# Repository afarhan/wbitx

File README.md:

# wifitalkie

A walkie-talkie on WiFi, on an ESP32-C3, that speaks through my.sbitx.net's
VoIP repeater. To my.sbitx.net it is one more radio of its owner's account,
always in the mode VOIP: the dial, FREQ, is the room, and whoever speaks on
that kilohertz, from a zBitx, an sBitx or another talkie, is heard here.

This first one is set from the laptop over USB, a verb a line.

## Build, upload, talk to it

    make                          # arduino-cli, esp32:esp32 3.3.0, ESP32-C3, USB CDC on boot
    make upload PORT=/dev/ttyACM0
    make monitor                  # tools/talkie.py: type verbs
    make check                    # host tests, against zbitxre's accounts/voip.py

`tools/talkie.py STATUS` sends one verb and prints what comes back.

## First time

    WIFI "my ssid" mypassword
    CALL VU2ESE
    FREQ 7074000
    KEY                           # add this at my.sbitx.net as one of your radios
    STATUS                        # SERVICE ONLINE vu2ese-talkie, VOIP 7074 KHZ, 2 HERE

The first connection stretches the key, some seconds; it is kept after that.

## Verbs

    WIFI <ssid> <password>    CALL <callsign>     GRID <locator>
    FREQ <hz>                 SERVER <host> [port]
    KEY                       NEW_KEY (twice within 5 s)
    VOIP ONLINE|OFFLINE       PTT ON|OFF          TONE ON|OFF
    VOL <0-100>               MIC <0-100>         LEVELS ON|OFF
    STATUS                    RESTART

What the talkie says by itself: `WIFI UP`, `SERVICE ...`, `ROOM 7074 KHZ, 3 HERE`,
`HEARD VU3XYZ`, `OVER VU3XYZ`, `BUSY VU3XYZ`, `PTT ON`, `PTT OFF: ONE MINUTE`.

## Wiring (ESP32-C3 SuperMini; pins.h)

| GPIO | |
|---|---|
| 3 (ADC1) | microphone: MAX9814 module output |
| 4 | earbuds: 10 Ω, then an LC low-pass of about 5 kHz (1 mH in series and 1 µF to ground for 32 Ω earbuds; 470 µH and 2.2 µF for 16 Ω), then 220 µF (+ toward the C3) to tip and ring; sleeve to ground |
| 9 | PTT: the BOOT button, to ground |
| 8 | lamp: the board's LED, lit while speaking or hearing |

## Where the protocol is written

zbitxre's `PROTOCOL.md` ("Authentication", "VoIP: the repeater"),
`accounts/voip.py` and `clients/remote/zbitx_remote.c`.
`wifitalkie/sha256.c` is zbitxre's `clients/remote/sha256.c`, as it is.

## Updating over WiFi

`firmware/wifitalkie.ino.bin` is the firmware as `make release` puts it
there, with `firmware/version.txt`, the time it was built.

From GitHub: on the talkie, joined to a network, Settings > Update... >
From github.com, ENTER. It takes the file if it is newer than its own and
restarts into it; otherwise it says Up to date. The serial command
`UPDATE GITHUB` does the same.

Locally, from a phone or laptop: Settings > Update... > Locally on the
talkie, join its access point TALKIE-<callsign>, open 192.168.4.1, type
the four-figure code the talkie shows, choose the file and SEND. The
talkie and the page both show how far it has got; when it says done,
close the page.

Either way, a firmware that does not start goes back to the old one by
itself.

## License

GPL-3.0-or-later; see LICENSE.

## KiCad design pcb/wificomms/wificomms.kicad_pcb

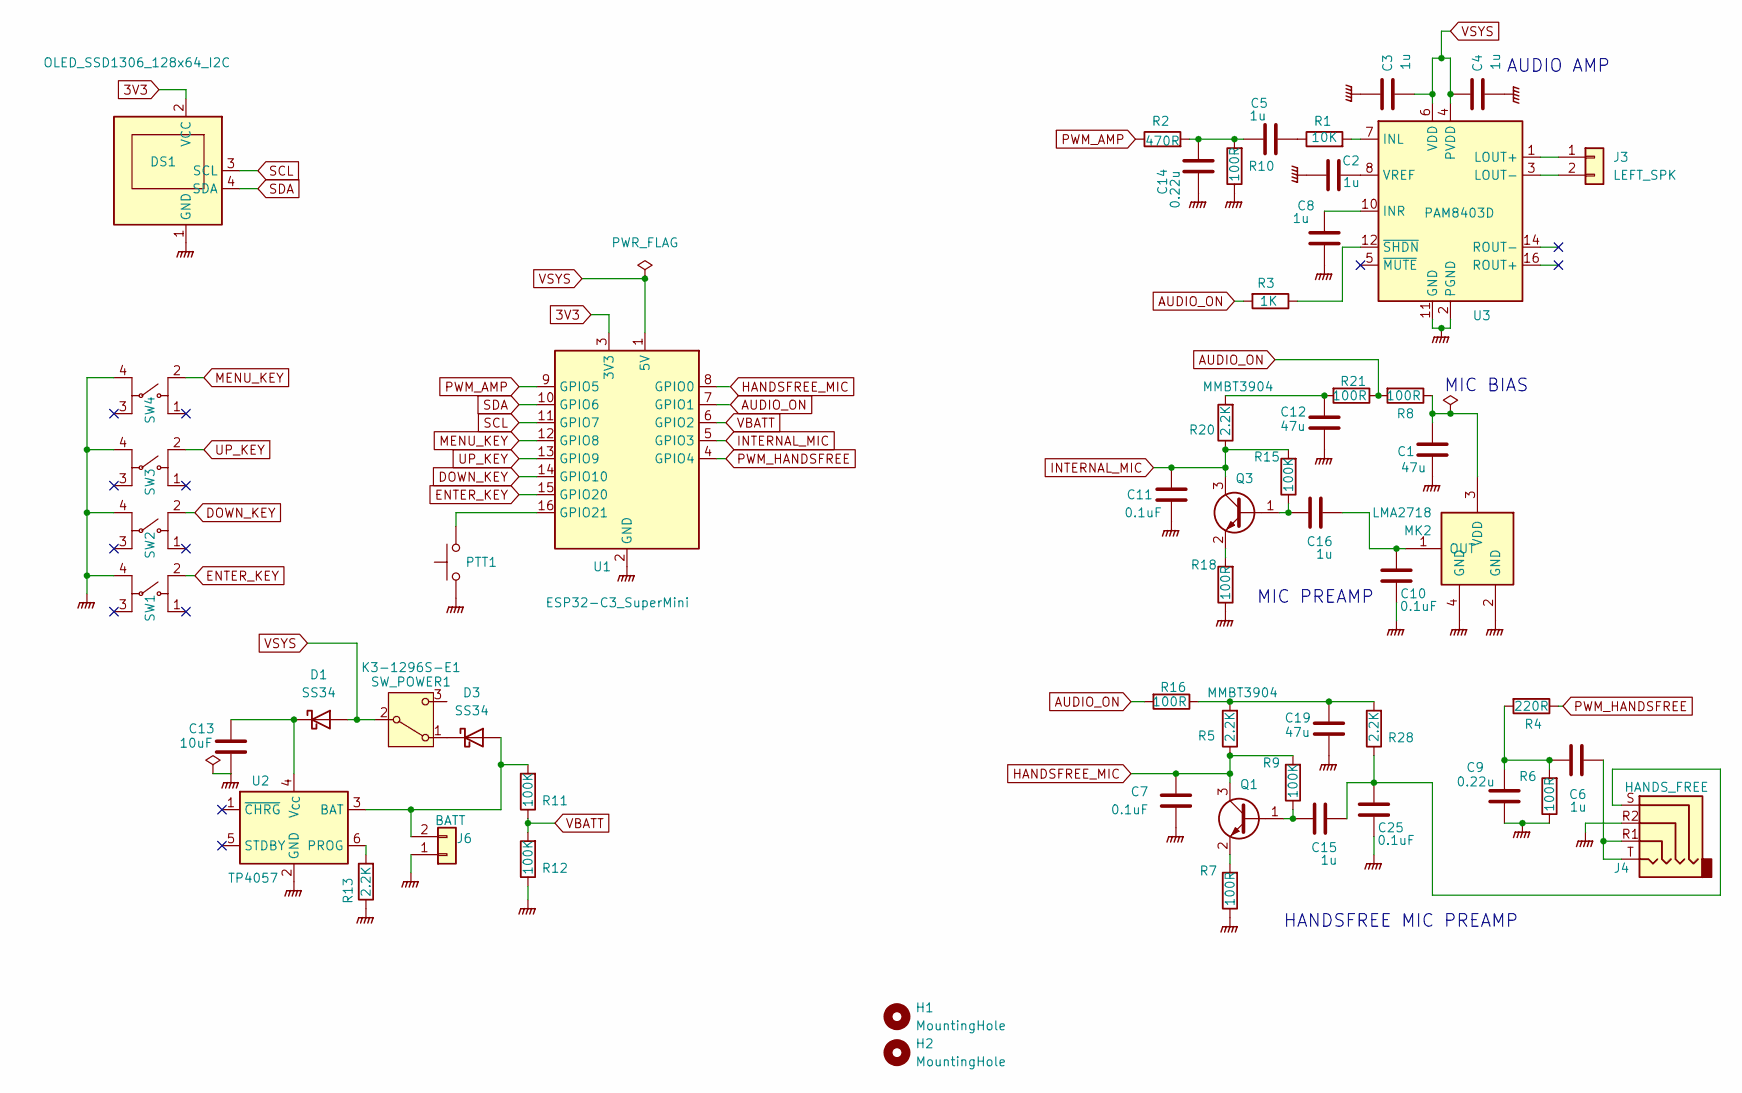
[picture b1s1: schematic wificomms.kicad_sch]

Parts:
C1, C12, C19: 47u; C_0805_2012Metric; LCSC C16780
C2, C3, C4, C5, C8: 1u; C_0805_2012Metric
C6, C15, C16: 1u; C_0805_2012Metric; LCSC C28323
C7, C10, C11, C25: 0.1uF; C_0805_2012Metric; LCSC C49678
C9: 0.22u; C_0805_2012Metric; LCSC C5378
C13: 10uF; C_0805_2012Metric; LCSC C15850
C14: 0.22u; C_0805_2012Metric
D1, D3: SS34; D_SMA; LCSC C8678
DS1: OLED_SSD1306_128x64_I2C
H1, H2: MountingHole; MountingHole_3.2mm_M3
J3: LEFT_SPK; PinHeader_1x02_P2.54mm_Vertical
J4: HANDS_FREE; Jack_3.5mm_PJ320D_Horizontal; LCSC C431535
J6: BATT; JST_PH_S2B-PH-SM4-TB_1x02-1MP_P2.00mm_Horizontal; LCSC C54582899
MK2: LMA2718; MEMS_LMA2718; LCSC C5373222
PTT1: SKRTLAE010; LCSC C110293
Q1, Q3: MMBT3904; SOT-23-3; LCSC C20526
R1: 10K; R_0805_2012Metric
R2: 470R; R_1206_3216Metric
R3: 1K; R_0805_2012Metric; LCSC C17520
R4: 220R; R_0805_2012Metric; LCSC C17557
R5, R13, R20, R28: 2.2K; R_0805_2012Metric; LCSC C17520
R6, R7, R8, R18: 100R; R_0805_2012Metric; LCSC C17408
R9, R15: 100K; R_0805_2012Metric; LCSC C149504
R10: 100R; R_0805_2012Metric
R11, R12: 100K; R_0805_2012Metric; LCSC C17520
R16, R21: 100R; R_0805_2012Metric; LCSC C17415
SW1, SW2, SW3, SW4: B3FS-1010P; LCSC C231324
SW_POWER1: K3-1296S-E1; LCSC C128955
U1: ESP32-C3_SuperMini
U2: TP4057; TSOT-23-6; LCSC C725791
U3: PAM8403D; SO-16_3.9x9.9mm_P1.27mm

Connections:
3V3: DS1.2 (VCC), U1.3 (3V3)
AUDIO_ON: R3.2, R8.2, R16.2, R21.1, U1.7 (GPIO1)
DOWN_KEY: SW2.2, U1.14 (GPIO10)
ENTER_KEY: SW1.2, U1.15 (GPIO20)
GNDPWR: C1.2, C2.1, C3.1, C4.2, C7.1, C8.1, C9.1, C10.1, C11.1, C12.2, C13.2, C14.1, C19.2, C25.1, DS1.1 (GND), J4.R2, J6.1, MK2.2 (GND), MK2.4 (GND), PTT1.1, R6.1, R7.1, R10.1, R12.1, R13.1, R18.1, SW1.4, SW2.4, SW3.4, SW4.4, U1.2 (GND), U2.2 (GND), U3.2 (PGND), U3.11 (GND), U3.15 (PGND)
HANDSFREE_MIC: C7.2, Q1.3 (C), R5.1, R9.2, U1.8 (GPIO0)
INTERNAL_MIC: C11.2, Q3.3 (C), R15.2, R20.1, U1.5 (GPIO3)
MENU_KEY: SW4.2, U1.12 (GPIO8)
unnamed: C5.2, R1.1
unnamed: C6.1, C9.2, R4.2, R6.2
unnamed: C6.2, J4.R1, J4.T
unnamed: C12.1, R20.2, R21.2
unnamed: C5.1, C14.2, R2.2, R10.2
unnamed: C15.2, C25.2, J4.S, R28.1
unnamed: C19.1, R5.2, R16.1, R28.2
unnamed: C13.1, D1.1 (K), U2.4 (V_{CC})
unnamed: D3.2 (A), J6.2, R11.2, U2.3 (BAT)
unnamed: D3.1 (K), SW_POWER1.1 (A)
unnamed: J3.1, U3.1 (LOUT+)
unnamed: J3.2, U3.3 (LOUT-)
unnamed: C10.2, C16.2, MK2.1 (OUT)
unnamed: C1.1, MK2.3 (VDD), R8.1
unnamed: C15.1, Q1.1 (B), R9.1
unnamed: Q1.2 (E), R7.2
unnamed: C16.1, Q3.1 (B), R15.1
unnamed: Q3.2 (E), R18.2
unnamed: PTT1.2, U1.16 (GPIO21)
unnamed: R13.2, U2.6 (PROG)
unnamed: R1.2, U3.7 (INL)
unnamed: C8.2, U3.10 (INR)
unnamed: C2.2, U3.8 (VREF)
unnamed: R3.1, U3.12 (~SHDN)
PWM_AMP: R2.1, U1.9 (GPIO5)
PWM_HANDSFREE: R4.1, U1.4 (GPIO4)
SCL: DS1.3 (SCL), U1.11 (GPIO7)
SDA: DS1.4 (SDA), U1.10 (GPIO6)
UP_KEY: SW3.2, U1.13 (GPIO9)
VBATT: R11.1, R12.2, U1.6 (GPIO2)
VSYS: C3.2, C4.1, D1.2 (A), SW_POWER1.2 (B), U1.1 (5V), U3.4 (PVDD), U3.6 (VDD), U3.13 (PVDD)

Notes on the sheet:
AUDIO AMP
HANDSFREE MIC PREAMP
MIC PREAMP
MIC BIAS

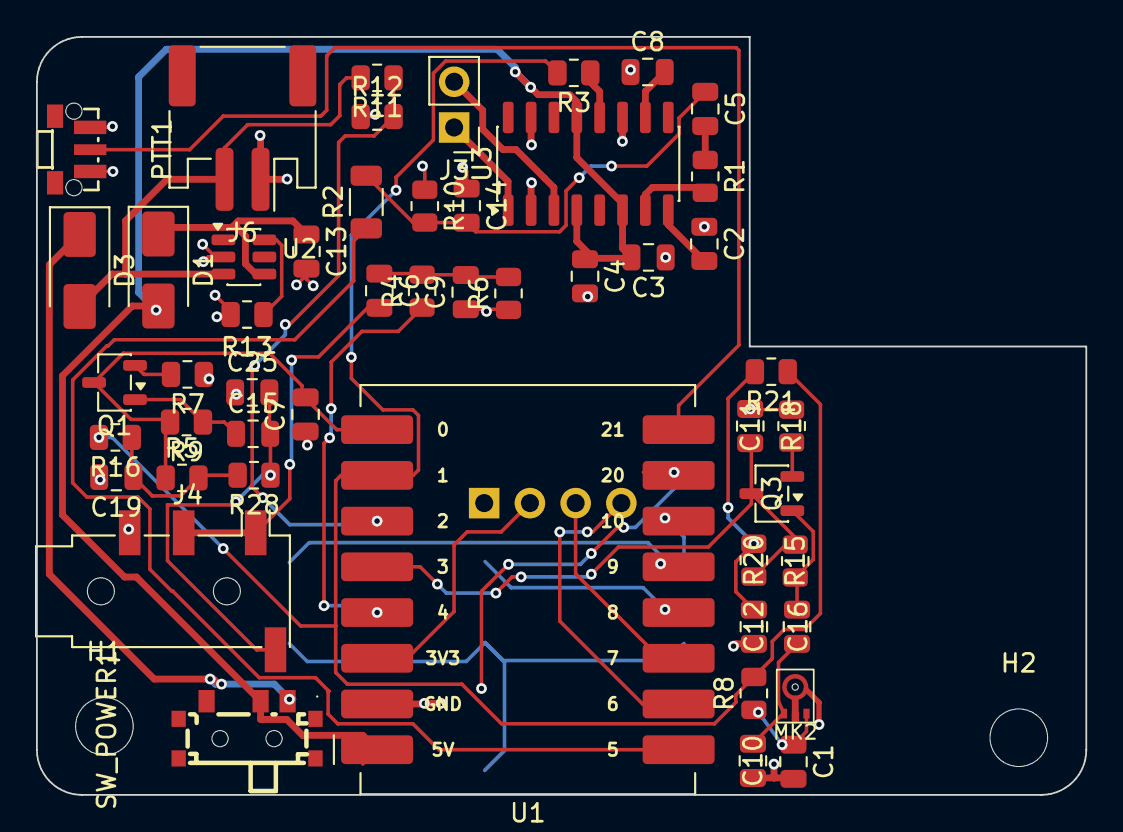
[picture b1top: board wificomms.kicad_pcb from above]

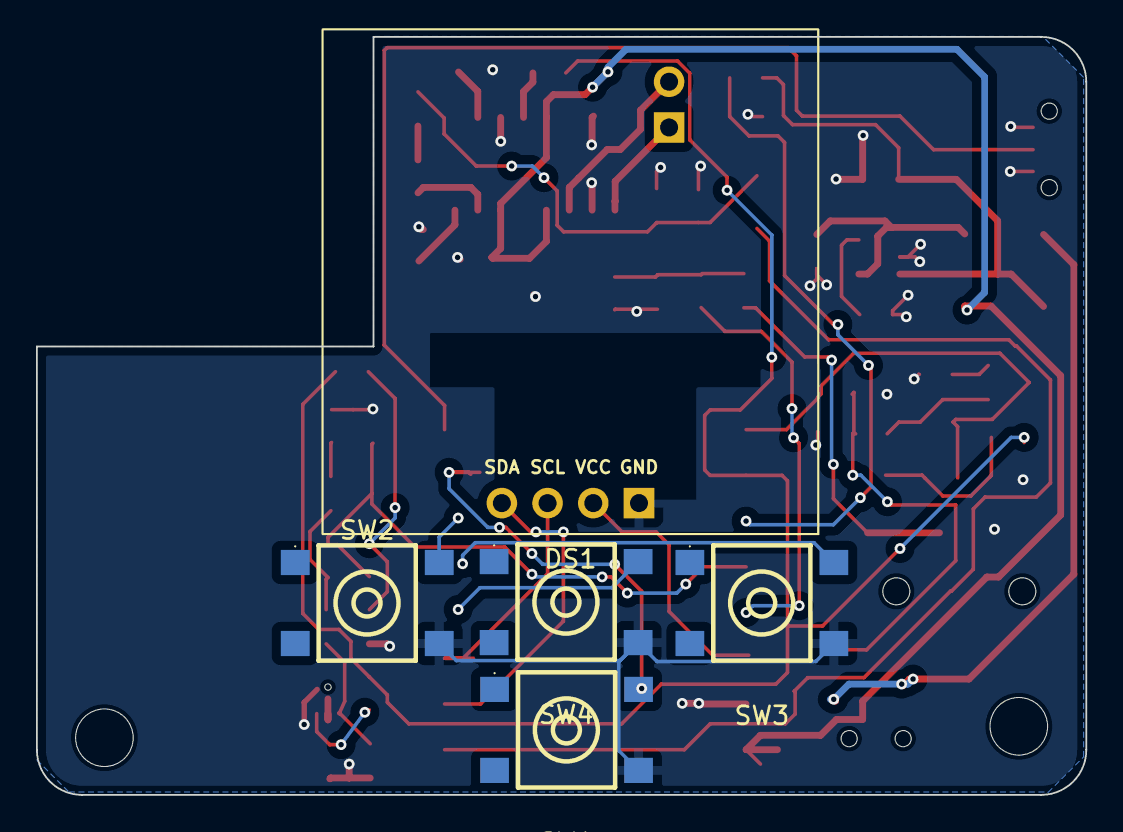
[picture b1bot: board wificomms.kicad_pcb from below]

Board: 2 copper layers, 58.3 x 42.1 mm, 57 parts (5 on the bottom side), 39 nets.

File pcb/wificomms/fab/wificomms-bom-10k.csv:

Comment,Designator,Footprint,LCSC Part #
47u,"C1,C12,C19",C_0805_2012Metric,C16780
1u,"C2,C3,C4,C5,C6,C8,C15,C16",C_0805_2012Metric,C28323
0.1uF,"C7,C10,C11,C25",C_0805_2012Metric,C49678
0.22u,"C9,C14",C_0805_2012Metric,C5378
10uF,C13,C_0805_2012Metric,C15850
SS34,"D1,D3",D_SMA,C8678
HANDS_FREE,J4,Jack_3.5mm_PJ320D_Horizontal,C431535
BATT,J6,JST_PH_S2B-PH-SM4-TB_1x02-1MP_P2.00mm_Horizontal,C54582899
LMA2718,MK2,MEMS_LMA2718,C5373222
SKRTLAE010,PTT1,SKRTLAE010,C110293
MMBT3904,"Q1,Q3",SOT-23-3,C20526
10K,"R1,R11,R12",R_0805_2012Metric,C17414
470R,R2,R_1206_3216Metric,C4502
1K,R3,R_0805_2012Metric,C17513
220R,R4,R_0805_2012Metric,C17557
2.2K,"R5,R13,R20,R28",R_0805_2012Metric,C17520
100R,"R6,R7,R8,R10,R16,R18,R21",R_0805_2012Metric,C17408
100K,"R9,R15",R_0805_2012Metric,C149504
B3FS-1010P,"SW1,SW2,SW3,SW4",B3FS-1010P,C231324
K3-1296S-E1,SW_POWER1,K3-1296S-E1,C128955
TP4057,U2,TSOT-23-6,C725791
PAM8403D,U3,SO-16_3.9x9.9mm_P1.27mm,C5122557

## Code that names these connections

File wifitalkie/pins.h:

// SPDX-License-Identifier: GPL-3.0-or-later
// Copyright (C) 2026 Ashhar Farhan
//
// pins.h — where the talkie's parts go on an ESP32-C3 SuperMini.
//
// The author's map of 31 October 2026, for his PCB. The microphones have to
// be on ADC1, GPIO0 to GPIO4: ADC2 cannot be read while the WiFi is on. The
// front panel, the display and four keys, is GPIO6 to GPIO10 and GPIO20, in
// a row on one edge, for one connector; the keys, top to bottom, MENU, UP,
// DOWN, ENTER. GPIO9 is also the board's BOOT button, so BOOT is UP once
// the board has started; GPIO8 is also its blue lamp, which lights while
// MENU is held, and the talkie's lamp is now on the display. ENTER is the
// PTT on the home page; the PTT key speaks on every page. GPIO4 and GPIO5
// are the headset's left and right.
// GPIO0 is the headset's microphone. GPIO1 powers both microphones'
// preamplifiers and holds the PAM8403's shutdown up through 4.7k: low,
// all three are off. The HW-104 module ties shutdown (pin 12) to PVDD
// (pin 13) in its copper, so pin 12 is lifted off its pad. GPIO2 reads the 5 V line through a 100k and 100k divider: the
// battery. GPIO21 is the PTT key, to ground; it is UART0's TX, driven
// by the ROM at reset, so the key wants 1k in series.

#pragma once

#define PIN_MICROPHONE 3
#define PIN_HEADSET_MIC 0
#define PIN_SPEAKER_LEFT 4
#define PIN_SPEAKER_RIGHT 5
#define PIN_DISPLAY_SDA 6
#define PIN_DISPLAY_SCL 7
#define PIN_KEY_MENU 20      // MENU and ENTER swapped, UP and DOWN swapped (the author's, 2026-11-23)
#define PIN_KEY_UP 10
#define PIN_KEY_DOWN 9
#define PIN_KEY_ENTER 8
#define PIN_KEY_PTT 21
#define PIN_MIC_POWER 1
#define PIN_BATTERY 2

// 0 on the hand-wired talkie, whose divider is on the 5 V line, the cell
// through a Schottky; 1 on the wificomms board, whose divider is on the
// cell itself, R11 and R12 made 10k and 10k (battery.c), and the USB
// cannot be told from it. Every wificomms board has its R11 and R12
// changed to 10k by hand, the author's of 2026-11-11, so 1 is for all.
#define BATTERY_DIVIDER_ON_CELL 1
